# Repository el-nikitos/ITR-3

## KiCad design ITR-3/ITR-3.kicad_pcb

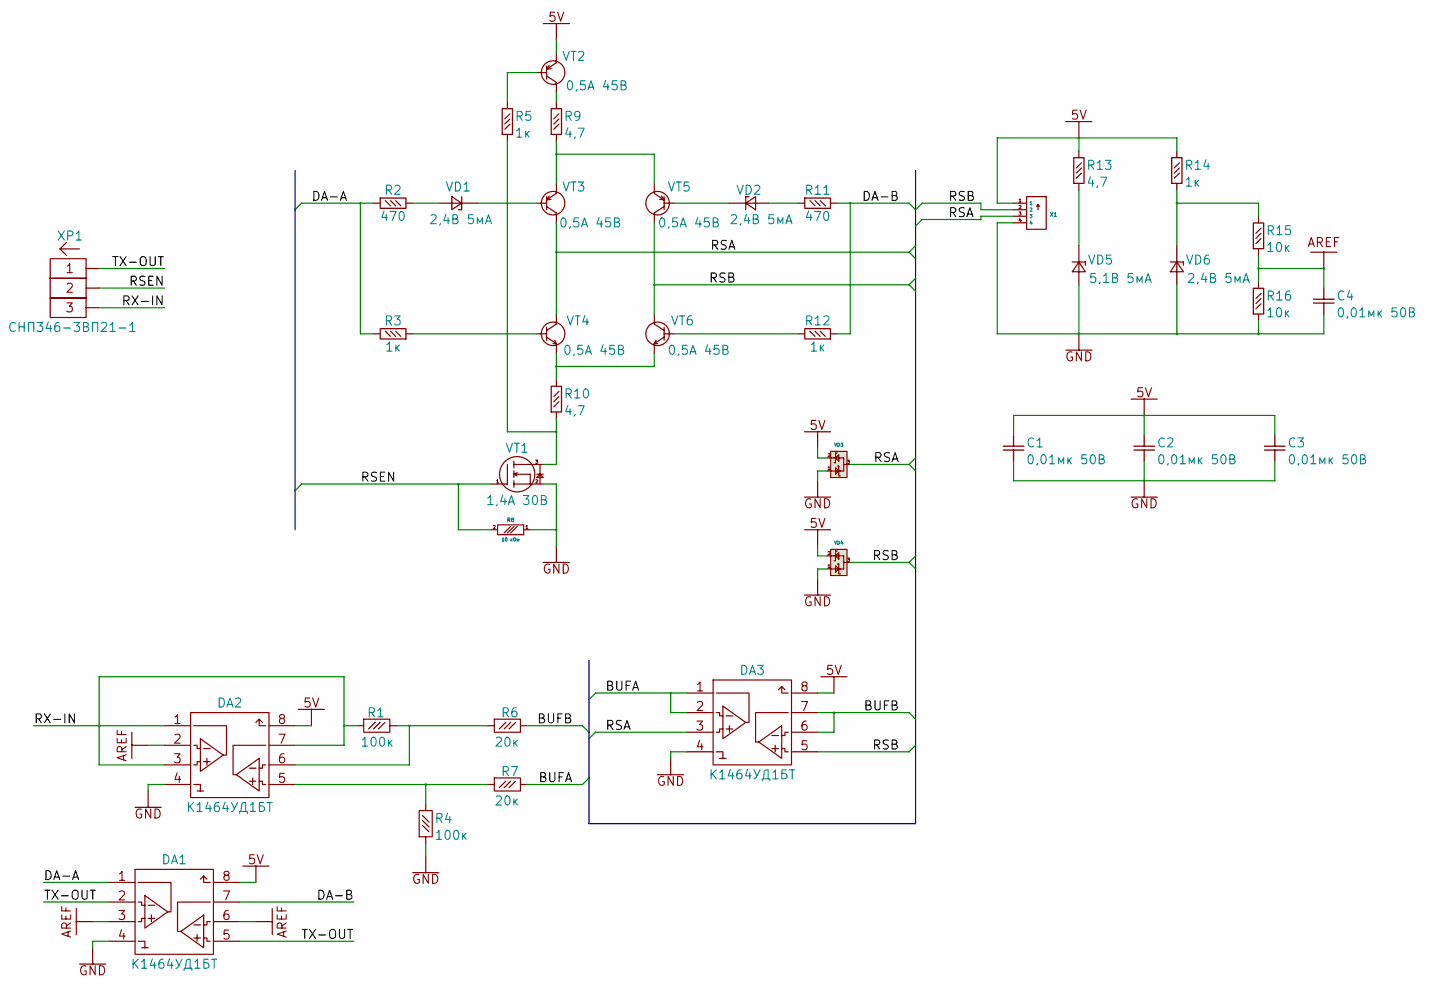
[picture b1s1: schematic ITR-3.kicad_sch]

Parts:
C1, C2, C3, C4: Конденсатор*0,1мкФ*25В*0603; Конденсатор_SMD_IEC_0603
DA1, DA2, DA3: ОУ*сдвоенный*so-8*ОТК; SO-8
R1, R4: smd-резистор*100к*0603*ВП; Резистор_SMD_IEC_0603-0,075_Вт
R2, R11: smd-резистор*470*0,1Вт*5проц*0603*ВП; Резистор_SMD_IEC_0603-0,1_Вт
R3, R5, R12, R14: smd-резистор*1к*0,1Вт*5проц*0603*ВП; Резистор_SMD_IEC_0603-0,1_Вт
R6, R7: smd-резистор*20к*0603*ВП; Резистор_SMD_IEC_0603-0,075_Вт
R8: Резистор_0,065Вт; Резистор_SMD_0603_0,065_Вт
R9, R10, R13: smd-резистор*4,7*0,1Вт*5проц*0603*ВП; Резистор_SMD_IEC_0603-0,1_Вт
R15, R16: smd-резистор*10к*0,1Вт*5проц*0603*ВП; Резистор_SMD_IEC_0603-0,1_Вт
VD1, VD2, VD5, VD6: smd-стабилитрон*5,1В*5мА*КД-36*ВП; Корпус_IEC_КД-36
VD3, VD4: Диоды_шоттки_BAT54S; Корпус_КТ-46
VT1: Транзистор_полевой_N-канальный_КП526А9; Корпус_КТ-46
VT2, VT3, VT5: Транзистор*pnp*0,5А*45В*SOT23; Корпус_КТ-46
VT4, VT6: Транзистор*npn*0,5А*45В*SOT23; Корпус_КТ-46
X1: Вилка_PLS4; Вилка_PLS4_вертикальная
XP1: Вилка*PLS*3контакта*1ряд*вертикальная; Вилка_SNP346-3VP21-1

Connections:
5V: C1.2, C2.2, C3.2, DA1.8, DA2.8, DA3.8, R13.2, R14.2, VD3.2, VD4.2, VT2.2, X1.1
/BUFA: DA3.1, DA3.2, R7.2
/BUFB: DA3.6, DA3.7, R6.2
/DA-A: DA1.1, R2.1, R3.2
/DA-B: DA1.7, R11.2, R12.1
/RSA: DA3.3, VD3.3, VT3.3, VT4.3, X1.3
/RSB: DA3.5, VD4.3, VT5.3, VT6.3, X1.2
/RSEN: R8.2, VT1.1, XP1.2A
/RX-IN: DA2.1, XP1.3A
/TX-OUT: DA1.2, DA1.5, XP1.1A
AREF: C4.2, DA1.3, DA1.6, DA2.2, R15.1, R16.2
GND: C1.1, C2.1, C3.1, C4.1, DA1.4, DA2.4, DA3.4, R4.1, R8.1, R16.1, VD3.1, VD4.1, VD5.A, VD6.A, VT1.2, X1.4
unnamed: DA2.3, DA2.7, R1.1
unnamed: DA2.5, R4.2, R7.1
unnamed: DA2.6, R1.2, R6.1
unnamed: R2.2, VD1.A
unnamed: R3.1, VT4.1
unnamed: R5.2, VT2.1
unnamed: R9.1, VT3.2, VT5.2
unnamed: R9.2, VT2.3
unnamed: R5.1, R10.1, VT1.3
unnamed: R10.2, VT4.2, VT6.2
unnamed: R11.1, VD2.A
unnamed: R12.2, VT6.1
unnamed: R13.1, VD5.K
unnamed: R14.1, R15.2, VD6.K
unnamed: VD1.K, VT3.1
unnamed: VD2.K, VT5.1

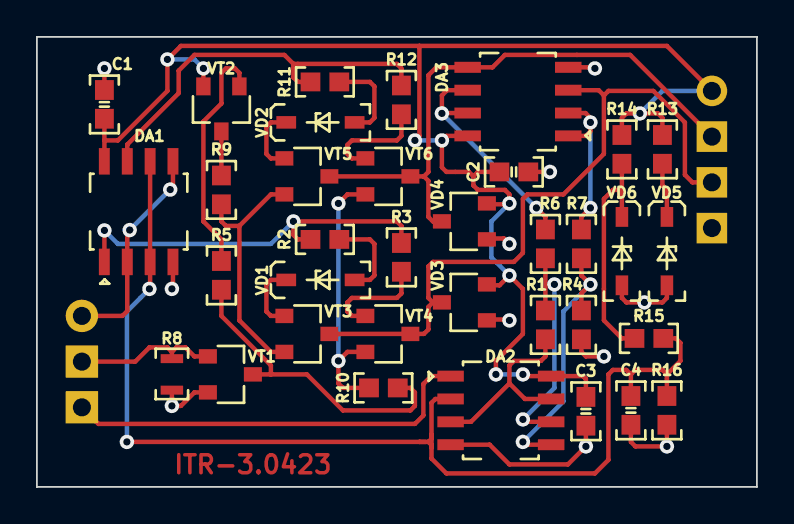
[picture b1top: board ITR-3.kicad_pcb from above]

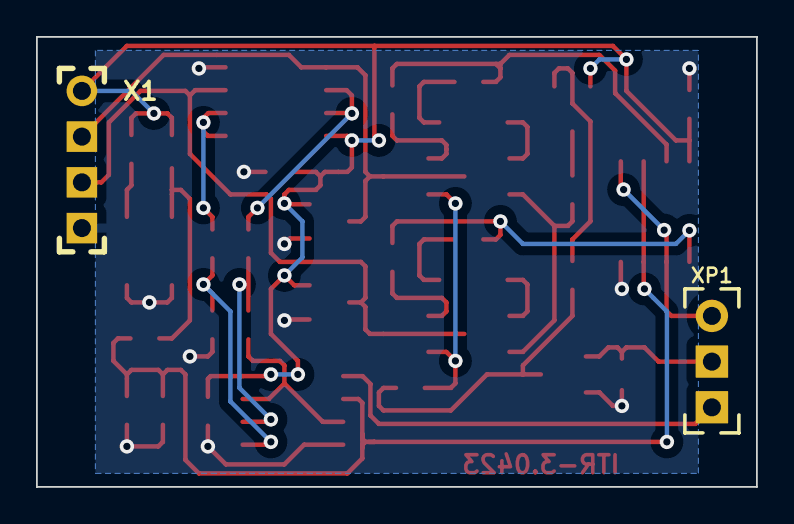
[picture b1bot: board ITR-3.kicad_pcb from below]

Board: 2 copper layers, 40.0 x 25.0 mm, 37 parts (2 on the bottom side), 28 nets.

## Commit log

2023-04-08 инициирован проект
2023-04-09 simone-модель
2023-04-09 обновлена схема - добавлен буферный входной ОУ
2023-04-11 подготовлена трассировка и GBR для заказа
